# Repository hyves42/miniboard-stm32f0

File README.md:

miniboard-stm32f0
=================

This is the simplest bare-minimum form of a protototyping board for the stm32f030 chip from S.T.

Here is what it looks like :

Front

Back

The orientation of the pin headers is only indicative. 

* The long pin header row is intended to be plugged into a breadboard - back side of the board facing up.
* Other pin headers can be soldered on either side of the board depending on the usage
* Quartz is optional
* Reset button can be soldered on top or bottom side (or both)

The board is made with Kicad and requires a 2015 version for editing (with .pretty footprint libraries support)

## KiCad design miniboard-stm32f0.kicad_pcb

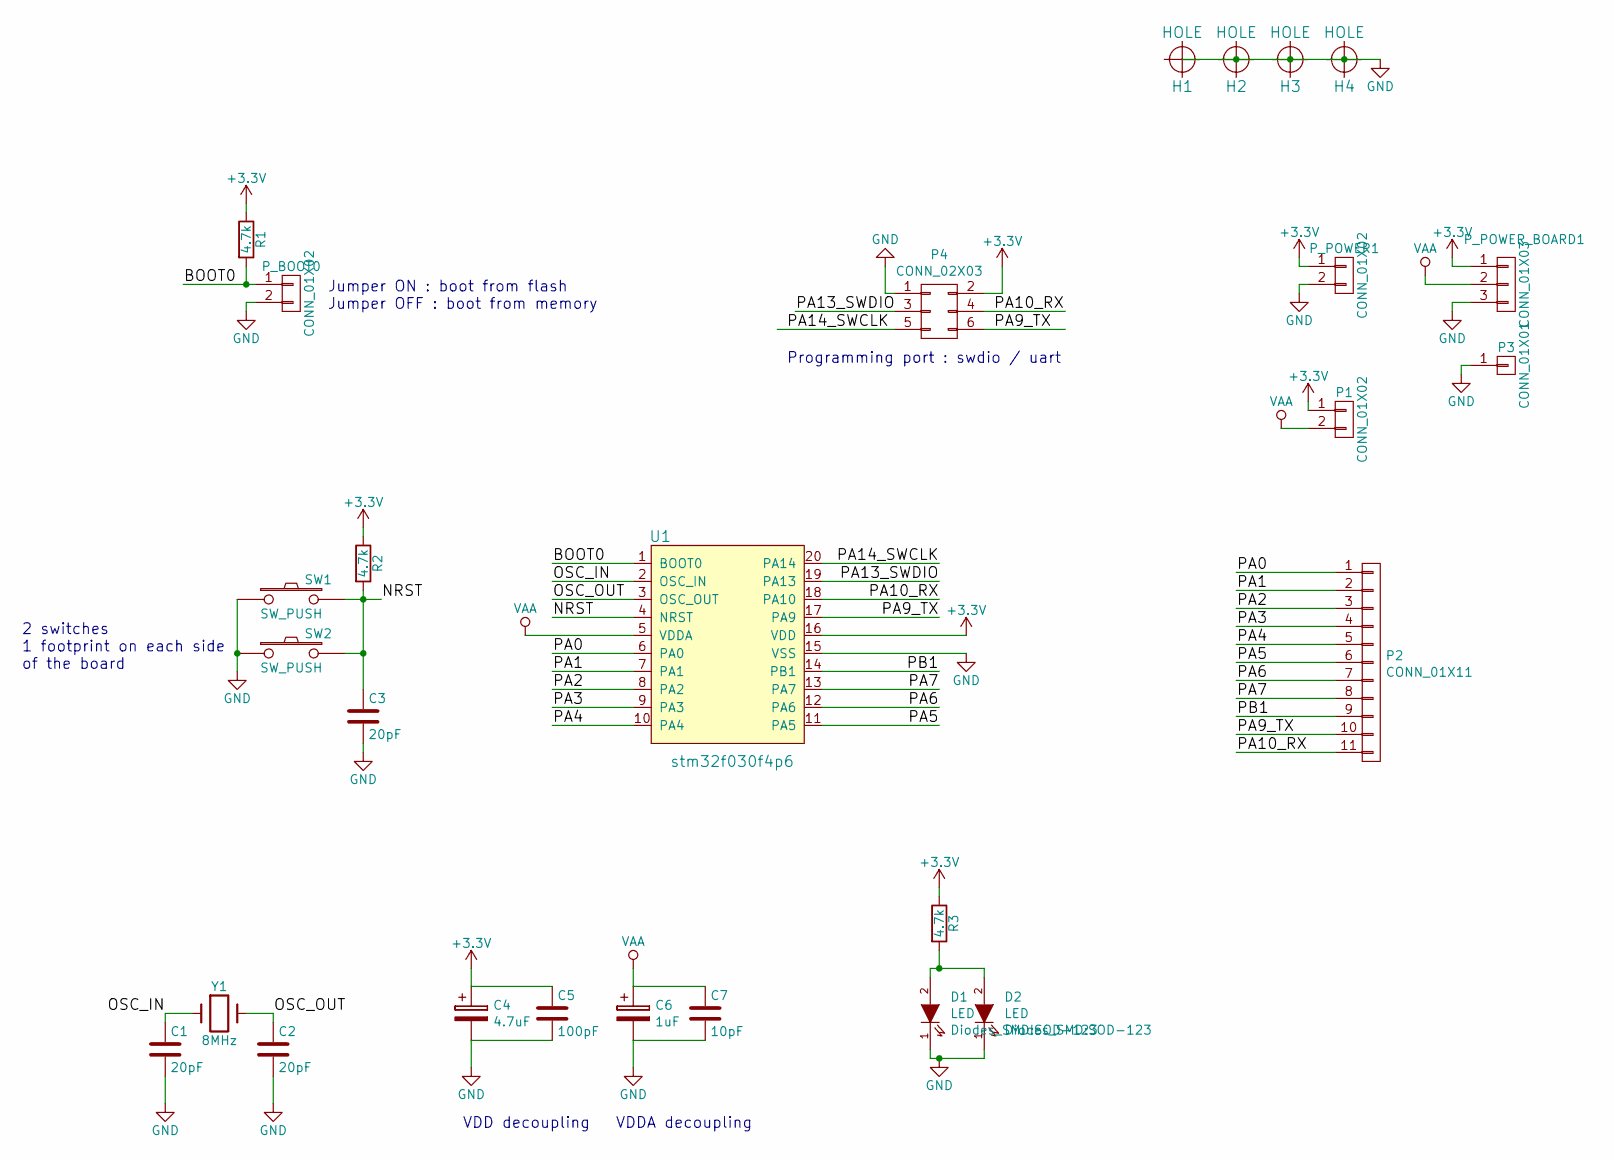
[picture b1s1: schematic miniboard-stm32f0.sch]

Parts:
C1, C2, C3: 20pF; C_0603
C4: 4.7uF; TantalC_SizeR_EIA-2012
C5: 100pF; C_0603
C6: 1uF; TantalC_SizeR_EIA-2012
C7: 10pF; C_0603
D1, D2: LED; SOD-123
H1, H2, H3, H4: HOLE; hole_2.5mm
P1: CONN_01X02; Pin_Header_Straight_1x02
P2: CONN_01X11; Pin_Header_Straight_1x11
P3: CONN_01X01; Pin_Header_Straight_1x01
P4: CONN_02X03; pin_header_edge_6
P_BOOT0: CONN_01X02; Pin_Header_Straight_1x02
P_POWER1: CONN_01X02; Pin_Header_Straight_1x02
P_POWER_BOARD1: CONN_01X03; Pin_Header_Straight_1x03
R1, R2, R3: 4.7k; R_0603
SW1, SW2: SW_PUSH; SW_SPST_EVQQ2
U1: stm32f030f4p6; tssop20
Y1: 8MHz; Crystal_HC49-U_Vertical

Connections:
+3V3: C4.1, C5.1, P1.1, P4.2, P_POWER1.1, P_POWER_BOARD1.1, R1.1, R2.1, R3.1, U1.16 (VDD)
/BOOT0: P_BOOT0.1, R1.2, U1.1 (BOOT0)
/NRST: C3.1, R2.2, SW1.2, SW2.2, U1.4 (NRST)
/OSC_IN: C1.1, U1.2 (OSC_IN), Y1.1
/OSC_OUT: C2.1, U1.3 (OSC_OUT), Y1.2
/PA0: P2.1, U1.6 (PA0)
/PA1: P2.2, U1.7 (PA1)
/PA2: P2.3, U1.8 (PA2)
/PA3: P2.4, U1.9 (PA3)
/PA4: P2.5, U1.10 (PA4)
/PA5: P2.6, U1.11 (PA5)
/PA6: P2.7, U1.12 (PA6)
/PA7: P2.8, U1.13 (PA7)
/PA9_TX: P2.10, P4.6, U1.17 (PA9)
/PA10_RX: P2.11, P4.4, U1.18 (PA10)
/PA13_SWDIO: P4.3, U1.19 (PA13)
/PA14_SWCLK: P4.5, U1.20 (PA14)
/PB1: P2.9, U1.14 (PB1)
GND: C1.2, C2.2, C3.2, C4.2, C5.2, C6.2, C7.2, D1.1 (K), D2.1 (K), H1.1, H2.1, H3.1, H4.1, P3.1, P4.1, P_BOOT0.2, P_POWER1.2, P_POWER_BOARD1.3, SW1.1, SW2.1, U1.15 (VSS)
unnamed: D1.2 (A), D2.2 (A), R3.2
VAA: C6.1, C7.1, P1.2, P_POWER_BOARD1.2, U1.5 (VDDA)

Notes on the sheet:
Jumper ON : boot from flash Jumper OFF : boot from memory
2 switches 1 footprint on each side of the board
VDD decoupling
VDDA decoupling
Programming port : swdio / uart

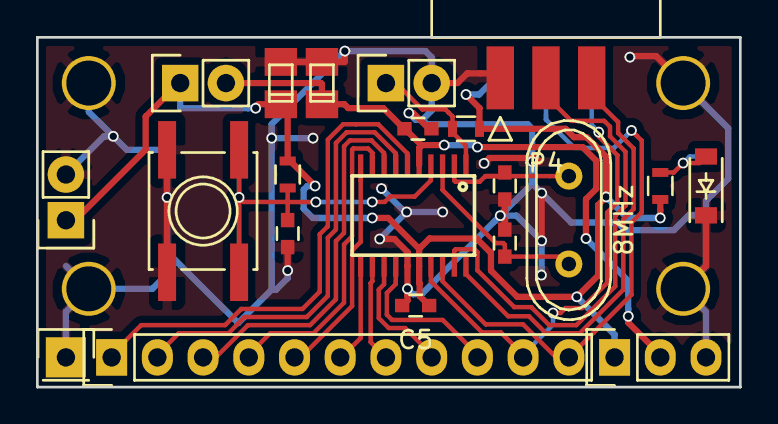
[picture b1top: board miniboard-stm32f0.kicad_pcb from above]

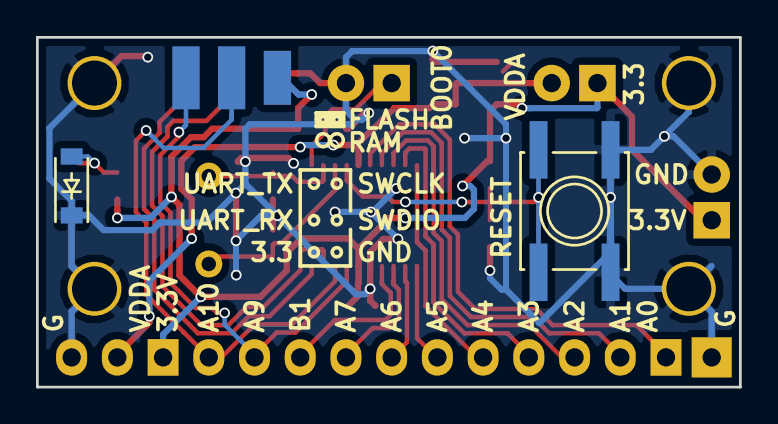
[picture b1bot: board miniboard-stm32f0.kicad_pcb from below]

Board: 2 copper layers, 39.1 x 19.4 mm, 27 parts (2 on the bottom side), 21 nets.

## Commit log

2015-10-13 Add stm32f0 lib
2015-10-13 Add kicad project
2015-10-14 1st version
2015-10-15 Change quartz footprint, add text
2015-10-15 Add oshw logo Generate missing gerber files
2015-10-15 Add screenshots and README.md
2015-10-15 Add MIT license
2015-10-15 move logo
2015-10-15 Fixed README text
2016-01-21 * Use edge connector for SWD and uart connector * Add power LED * Fix reset button footprint * Add decoupling caps * Realign power connector
2016-01-22 Fix minor routing issues Redraw mask
2016-01-24 Change direction of power connector
2016-02-24 Generate gerbers and export to pdf
2016-03-10 Fix footprint for the stm32 and the edge connector
